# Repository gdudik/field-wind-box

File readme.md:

# Programming the main controller board (USB-PD controller setup)

I am using a cheapo CH134A programmer board with an alligator clamp for SOIC-8. Example: https://a.co/d/9YnwEmc. This unit needed to be modded per the included instructions to work with an EEPROM chip running at 3.3v.

Binary file `USB_C_PD_controller.bin` was built using the TI Application Customization Tool at https://www.ti.com/tool/USBCPD-APPLICATION-CUSTOMIZATION-TOOL.

Choices used:
- Device Type: TPS25751
- Choose TPS 25751S under _Are you a 5V @ 3A power source (provider) only?_
- Highest supported USB Speed: USB 2
- Preferred data role: Device/Upstream Facing Port
- Support BC 1.2? No
- Liquid detection on Type C Connector? No
- Vendor ID and Desired Product ID: TI Vendor ID/0x0000 Product ID

After downloading the bin file from the tool, I used IMS_Prog which is a tool for Mac that will interface with the CH134A. On PC there are other tools, but you'll have to Google. IMS_Prog supposedly also works on Linux.

# Wiring

## 4-Pin Header to XLR
| 4 Pin Header | Wire Color  | Function  | XLR Pin Num  |
|---|---|---|---|
| 1  | Red  | Wind Gauge +12v  | 2  |
|  2 | Black  | Wind Gauge Pwr GND  | Shell  |
| 3  | Green  | Data RX from WG  | 3  |
|  4 |  White | Data GND  | 1  |

## 3-Pin Header to LP16 for RS232
| 3 Pin Header | Wire Color  | Function  | LP16 Pin Num  |
|---|---|---|---|
| 1  | Orange  | RXI  | 2  |
|  2 | White  | Data GND  | 3  |
| 3  | Blue  | TXO  | 1  |

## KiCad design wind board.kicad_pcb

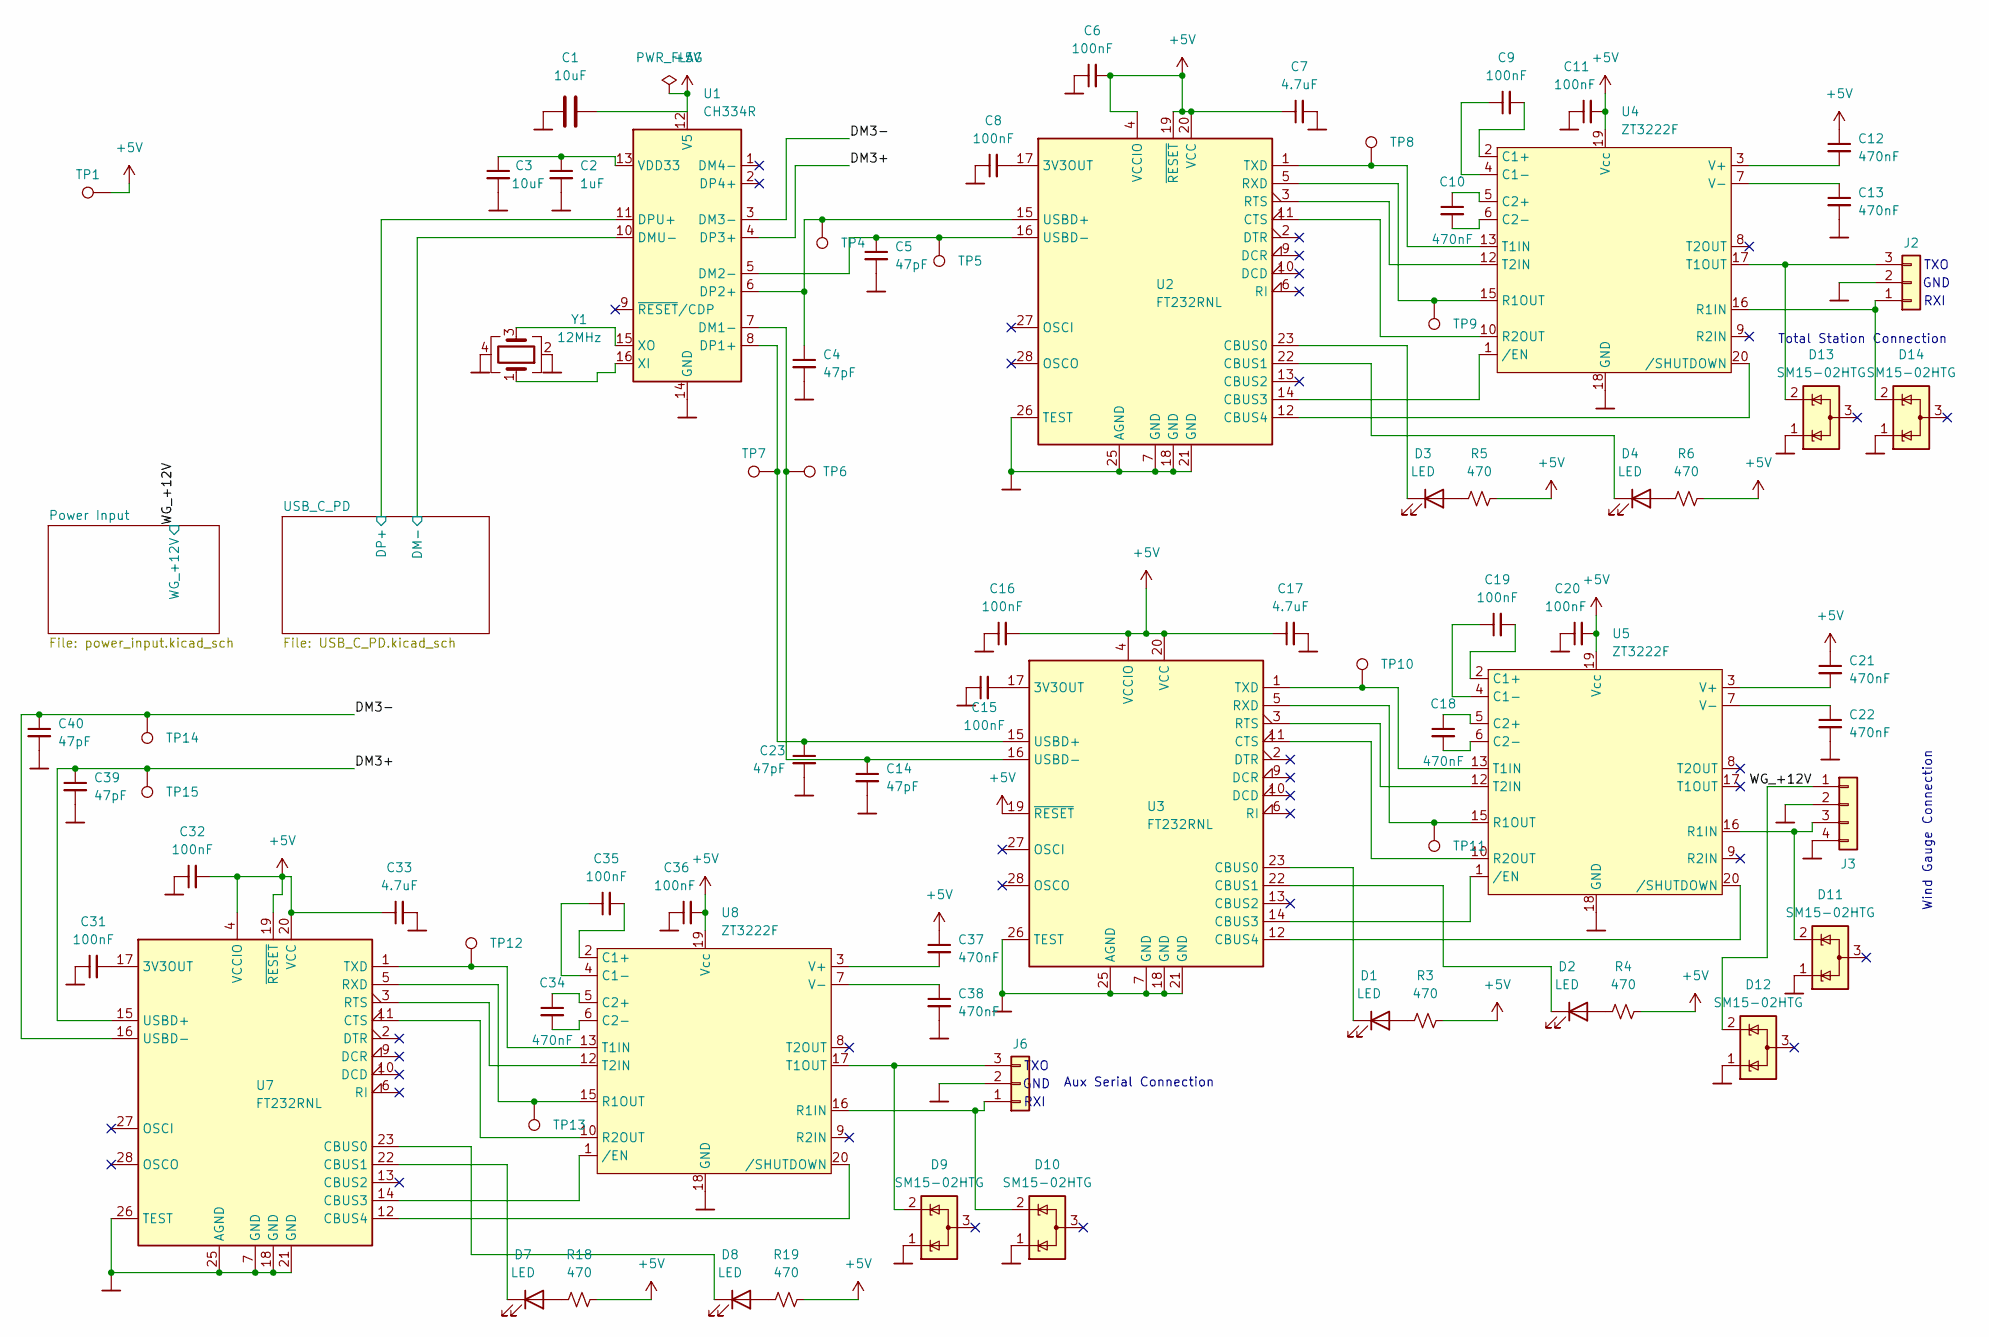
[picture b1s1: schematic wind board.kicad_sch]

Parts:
C1, C3: 10uF; C_0402_1005Metric
C2: 1uF; C_0402_1005Metric
C4, C5: 47pF; C_0603_1608Metric
C6, C8, C9, C11, C15, C16, C19, C20, C31, C32, C35, C36: 100nF; C_0402_1005Metric
C7, C33: 4.7uF; C_0603_1608Metric
C10, C12, C13, C18, C21, C22, C34, C37, C38: 470nF; C_0603_1608Metric
C14, C23, C39, C40: 47pF; C_0402_1005Metric
C17: 4.7uF; C_0402_1005Metric
D1, D2, D3, D4, D7, D8: LED; LED_0603_1608Metric
D9, D10, D11, D12, D13, D14: SM15-02HTG; SM0502HTG
J2, J6: Conn_01x06_MountingPin; PinHeader_1x03_P2.54mm_Horizontal
J3: Conn_01x06_MountingPin; PinHeader_1x04_P2.54mm_Horizontal
R3, R4, R5, R6, R18, R19: 470; R_0402_1005Metric
TP1, TP4, TP5, TP6, TP7, TP8, TP9, TP10, TP11, TP12, TP13, TP14, TP15: TestPoint; TestPoint_THTPad_1.0x1.0mm_Drill0.5mm
U1: CH334R; QSOP-16_3.9x4.9mm_P0.635mm
U2, U3, U7: FT232RNL; SSOP-28_5.3x10.2mm_P0.65mm
U4, U5, U8: ZT3222F; TSSOP-20_4.4x6.5mm_P0.65mm
Y1: 12MHz; Crystal_SMD_3225-4Pin_3.2x2.5mm

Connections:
+5V: C1.2, C6.2, C7.1, C11.2, C12.1, C16.2, C17.1, C20.2, C21.1, C32.2, C33.1, C36.2, C37.1, R3.2, R4.2, R5.2, R6.2, R18.2, R19.2, TP1.1, U1.12 (V5), U2.4 (VCCIO), U2.19 (~RESET), U2.20 (VCC), U3.4 (VCCIO), U3.19 (~RESET), U3.20 (VCC), U4.19 (Vcc), U5.19 (Vcc), U7.4 (VCCIO), U7.19 (~RESET), U7.20 (VCC), U8.19 (Vcc); also elsewhere on the board
/DM3+: C39.1, TP15.1, U1.4 (DP3+), U7.15 (USBD+)
/DM3-: C40.1, TP14.1, U1.3 (DM3-), U7.16 (USBD-)
/USB_C_PD/DM-: U1.10 (DMU-); also elsewhere on the board
/USB_C_PD/DP+: U1.11 (DPU+); also elsewhere on the board
/WG_+12V: D12.2 (K), J3.1; also elsewhere on the board
unnamed: D1.2 (A), R3.1
unnamed: D1.1 (K), U3.23 (CBUS0)
unnamed: D2.2 (A), R4.1
unnamed: D2.1 (K), U3.22 (CBUS1)
unnamed: D3.2 (A), R5.1
unnamed: D3.1 (K), U2.23 (CBUS0)
unnamed: D4.2 (A), R6.1
unnamed: D4.1 (K), U2.22 (CBUS1)
unnamed: D7.2 (A), R18.1
unnamed: D7.1 (K), U7.22 (CBUS1)
unnamed: D8.2 (A), R19.1
unnamed: D8.1 (K), U7.23 (CBUS0)
unnamed: D14.2 (K), J2.1, U4.16 (R1IN)
unnamed: D13.2 (K), J2.3, U4.17 (T1OUT)
unnamed: D11.2 (K), J3.3, U5.16 (R1IN)
unnamed: D10.2 (K), J6.1, U8.16 (R1IN)
unnamed: D9.2 (K), J6.3, U8.17 (T1OUT)
unnamed: C14.1, TP6.1, U1.7 (DM1-), U3.16 (USBD-)
unnamed: C5.1, TP5.1, U1.5 (DM2-), U2.16 (USBD-)
unnamed: C23.1, TP7.1, U1.8 (DP1+), U3.15 (USBD+)
unnamed: C4.1, TP4.1, U1.6 (DP2+), U2.15 (USBD+)
unnamed: C2.1, C3.1, U1.13 (VDD33)
unnamed: U1.16 (XI), Y1.1
unnamed: U1.15 (XO), Y1.3
unnamed: C8.2, U2.17 (3V3OUT)
unnamed: U2.14 (CBUS3), U4.1 (/EN)
unnamed: U2.12 (CBUS4), U4.20 (/SHUTDOWN)
unnamed: U2.11 (CTS), U4.10 (R2OUT)
unnamed: U2.3 (RTS), U4.12 (T2IN)
unnamed: TP9.1, U2.5 (RXD), U4.15 (R1OUT)
unnamed: TP8.1, U2.1 (TXD), U4.13 (T1IN)
unnamed: C15.2, U3.17 (3V3OUT)
unnamed: U3.14 (CBUS3), U5.1 (/EN)
unnamed: U3.12 (CBUS4), U5.20 (/SHUTDOWN)
unnamed: U3.11 (CTS), U5.10 (R2OUT)
unnamed: U3.3 (RTS), U5.12 (T2IN)
unnamed: TP11.1, U3.5 (RXD), U5.15 (R1OUT)
unnamed: TP10.1, U3.1 (TXD), U5.13 (T1IN)
unnamed: C9.2, U4.2 (C1+)
unnamed: C9.1, U4.4 (C1-)
unnamed: C10.1, U4.5 (C2+)
unnamed: C10.2, U4.6 (C2-)
unnamed: C12.2, U4.3 (V+)
unnamed: C13.1, U4.7 (V-)
unnamed: C19.2, U5.2 (C1+)
unnamed: C19.1, U5.4 (C1-)
unnamed: C18.1, U5.5 (C2+)
unnamed: C18.2, U5.6 (C2-)
unnamed: C21.2, U5.3 (V+)
unnamed: C22.1, U5.7 (V-)
unnamed: C31.2, U7.17 (3V3OUT)
unnamed: U7.14 (CBUS3), U8.1 (/EN)
unnamed: U7.12 (CBUS4), U8.20 (/SHUTDOWN)
unnamed: U7.11 (CTS), U8.10 (R2OUT)
unnamed: U7.3 (RTS), U8.12 (T2IN)
unnamed: TP13.1, U7.5 (RXD), U8.15 (R1OUT)
unnamed: TP12.1, U7.1 (TXD), U8.13 (T1IN)
unnamed: C35.2, U8.2 (C1+)
unnamed: C35.1, U8.4 (C1-)
unnamed: C34.1, U8.5 (C2+)
unnamed: C34.2, U8.6 (C2-)
unnamed: C37.2, U8.3 (V+)
unnamed: C38.1, U8.7 (V-)
~: C1.1, C2.2, C3.2, C4.2, C5.2, C6.1, C7.2, C8.1, C11.1, C13.2, C14.2, C15.1, C16.1, C17.2, C20.1, C22.2, C23.2, C31.1, C32.1, C33.2, C36.1, C38.2, C39.2, C40.2, D9.1 (K), D10.1 (K), D11.1 (K), D12.1 (K), D13.1 (K), D14.1 (K), J2.2, J3.2, J3.4, J6.2, U1.14 (GND), U2.7 (GND), U2.18 (GND), U2.21 (GND), U2.25 (AGND), U2.26 (TEST), U3.7 (GND), U3.18 (GND), U3.21 (GND), U3.25 (AGND), U3.26 (TEST), U4.18 (GND), U5.18 (GND), U7.7 (GND), U7.18 (GND), U7.21 (GND), U7.25 (AGND), U7.26 (TEST), U8.18 (GND), Y1.2, Y1.4; also elsewhere on the board

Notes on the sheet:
Total Station Connection
Aux Serial Connection
GND
TXO
Wind Gauge Connection
RXI

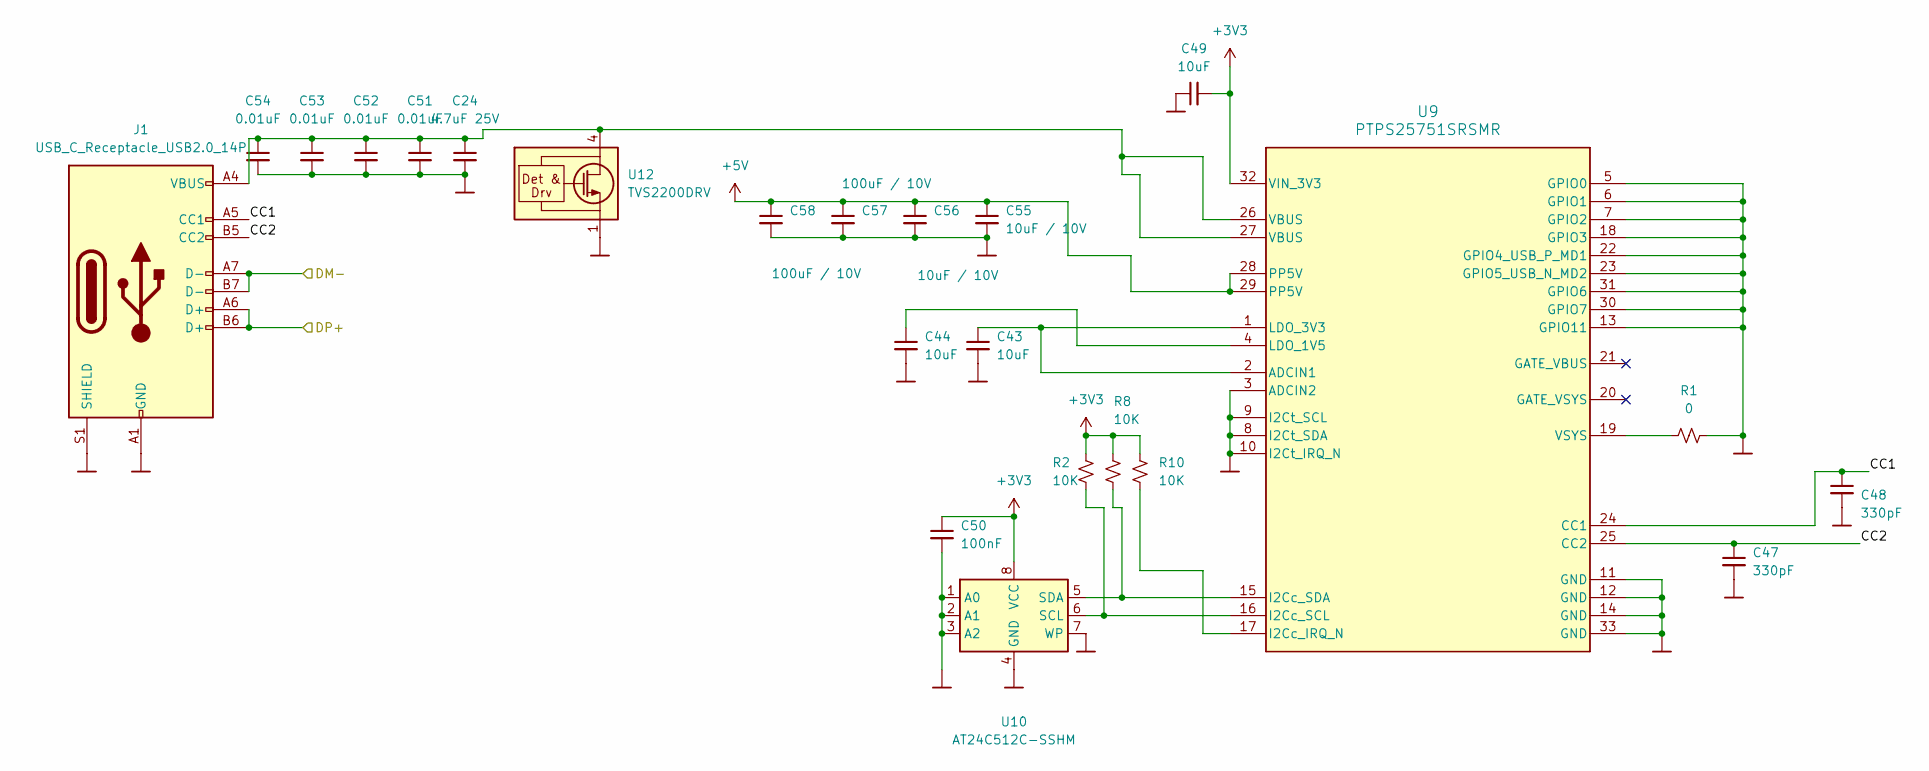
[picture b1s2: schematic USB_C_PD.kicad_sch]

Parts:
C24: 4.7uF 25V; C_0805_2012Metric
C43, C44, C49: 10uF; C_0402_1005Metric
C47, C48: 330pF; C_0603_1608Metric
C50: 100nF; C_0402_1005Metric
C51, C52, C53, C54: 0.01uF; C_0402_1005Metric
C55, C56: 10uF / 10V; C_0603_1608Metric
C57, C58: 100uF / 10V; C_1206_3216Metric
J1: USB_C_Receptacle_USB2.0_14P; USB_C_Receptacle_HRO_TYPE-C-31-M-12
R1: 0; R_0402_1005Metric
R2, R8, R10: 10K; R_0402_1005Metric
U9: PTPS25751SRSMR; RSM0032B-IPC_A
U10: AT24C512C-SSHM; SOIC-8_3.9x4.9mm_P1.27mm
U12: TVS2200DRV; WSON-6-1EP_2x2mm_P0.65mm_EP1x1.6mm

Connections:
+3V3: C49.2, C50.1, R2.1, R8.1, R10.1, U9.32 (VIN_3V3), U10.8 (VCC); also elsewhere on the board
+5V: C55.1, C56.1, C57.1, C58.1, U9.28 (PP5V), U9.29 (PP5V); also elsewhere on the board
/USB_C_PD/CC1: C48.1, J1.A5 (CC1), U9.24 (CC1)
/USB_C_PD/CC2: C47.1, J1.B5 (CC2), U9.25 (CC2)
/USB_C_PD/DM-: J1.A7 (D-), J1.B7 (D-); also elsewhere on the board
/USB_C_PD/DP+: J1.A6 (D+), J1.B6 (D+); also elsewhere on the board
unnamed: C24.1, C51.1, C52.1, C53.1, C54.1, J1.A4 (VBUS), J1.A9 (VBUS), J1.B4 (VBUS), J1.B9 (VBUS), U9.26 (VBUS), U9.27 (VBUS), U12.4 (IN), U12.5 (IN), U12.6 (IN)
unnamed: C43.1, U9.1 (LDO_3V3), U9.2 (ADCIN1)
unnamed: R10.2, U9.17 (I2Cc_IRQ_N)
unnamed: C44.1, U9.4 (LDO_1V5)
unnamed: R1.2, U9.19 (VSYS)
unnamed: R2.2, U9.16 (I2Cc_SCL), U10.6 (SCL)
unnamed: R8.2, U9.15 (I2Cc_SDA), U10.5 (SDA)
~: C24.2, C43.2, C44.2, C47.2, C48.2, C49.1, C50.2, C51.2, C52.2, C53.2, C54.2, C55.2, C56.2, C57.2, C58.2, J1.A1 (GND), J1.A12 (GND), J1.B1 (GND), J1.B12 (GND), J1.S1 (SHIELD), R1.1, U9.3 (ADCIN2), U9.5 (GPIO0), U9.6 (GPIO1), U9.7 (GPIO2), U9.8 (I2Ct_SDA), U9.9 (I2Ct_SCL), U9.10 (I2Ct_IRQ_N), U9.11 (GND), U9.12 (GND), U9.13 (GPIO11), U9.14 (GND), U9.18 (GPIO3), U9.22 (GPIO4_USB_P_MD1), U9.23 (GPIO5_USB_N_MD2), U9.30 (GPIO7), U9.31 (GPIO6), U9.33 (GND), U10.1 (A0), U10.2 (A1), U10.3 (A2), U10.4 (GND), U10.7 (WP), U12.1 (GND), U12.2 (GND), U12.3 (GND), U12.7 (GND); also elsewhere on the board

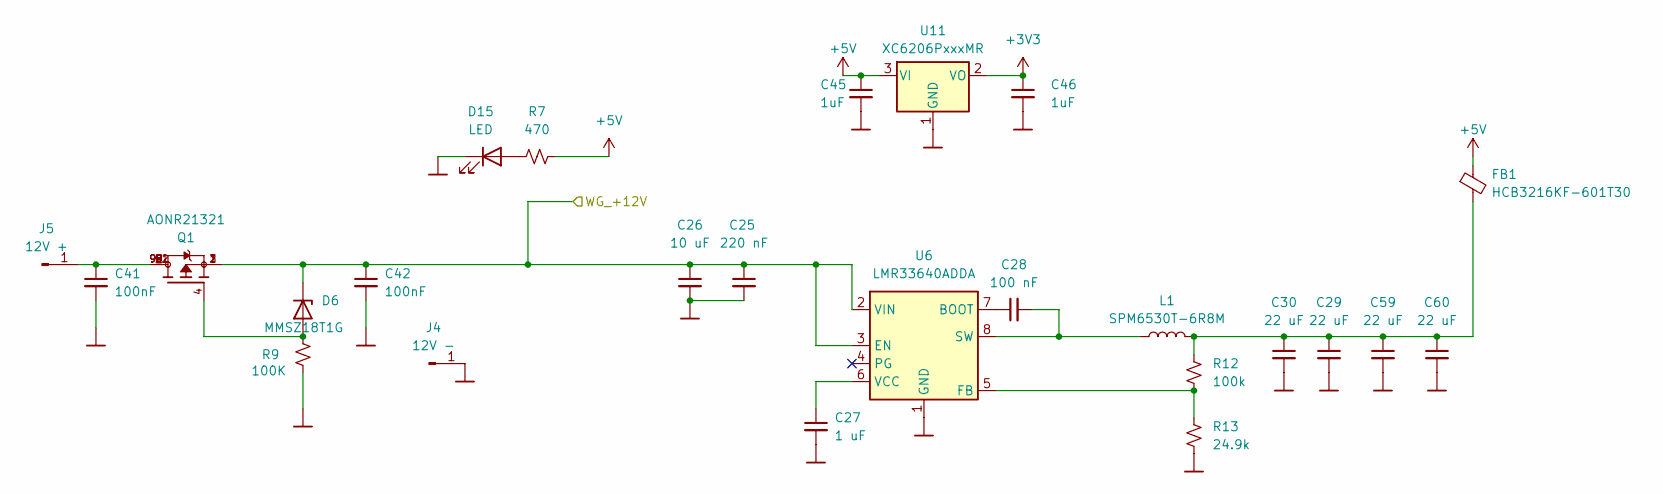
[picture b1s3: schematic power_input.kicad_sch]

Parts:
C25: 220 nF; C_0402_1005Metric
C26: 10 uF; C_0402_1005Metric
C27: 1 uF; C_0402_1005Metric
C28: 100 nF; C_0402_1005Metric
C29, C30, C59, C60: 22 uF; C_0402_1005Metric
C41, C42: 100nF; C_0402_1005Metric
C45, C46: 1uF; C_0402_1005Metric
D6: MMSZ18T1G; D_SOD-123
D15: LED; LED_0603_1608Metric
FB1: HCB3216KF-601T30; C_1206_3216Metric
J4: 12V -; MountingHole_4.3mm_M4_ISO7380_Pad_TopBottom
J5: 12V +; MountingHole_4.3mm_M4_ISO7380_Pad_TopBottom
L1: SPM6530T-6R8M; IND_SPM6530T-2R2M
Q1: AONR21321; TRANS_AONR21321; PARTREV 1.0
R7: 470; R_0402_1005Metric
R9: 100K; R_0402_1005Metric
R12: 100k; C_0402_1005Metric
R13: 24.9k; R_0402_1005Metric
U6: LMR33640ADDA; Texas_HSOP-8-1EP_3.9x4.9mm_P1.27mm_ThermalVias
U11: XC6206PxxxMR; SOT-23-3

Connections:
+3V3: C46.1, U11.2 (VO); also elsewhere on the board
+5V: C45.1, FB1.1, R7.2, U11.3 (VI); also elsewhere on the board
/WG_+12V: C25.1, C26.1, C42.1, D6.1 (K), Q1.1, Q1.2, Q1.3, U6.2 (VIN), U6.3 (EN); also elsewhere on the board
unnamed: C29.1, C30.1, C59.1, C60.1, FB1.2, L1.2, R12.1
unnamed: D6.2 (A), Q1.4, R9.2
unnamed: D15.2 (A), R7.1
unnamed: C41.1, J5.1, Q1.5, Q1.6, Q1.7, Q1.8, Q1.9, Q1.9_1, Q1.9_2
unnamed: C28.1, U6.7 (BOOT)
unnamed: R12.2, R13.1, U6.5 (FB)
unnamed: C28.2, L1.1, U6.8 (SW)
unnamed: C27.1, U6.6 (VCC)
~: C25.2, C26.2, C27.2, C29.2, C30.2, C41.2, C42.2, C45.2, C46.2, C59.2, C60.2, D15.1 (K), J4.1, R9.1, R13.2, U6.1 (GND), U6.9 (GND), U11.1 (GND); also elsewhere on the board

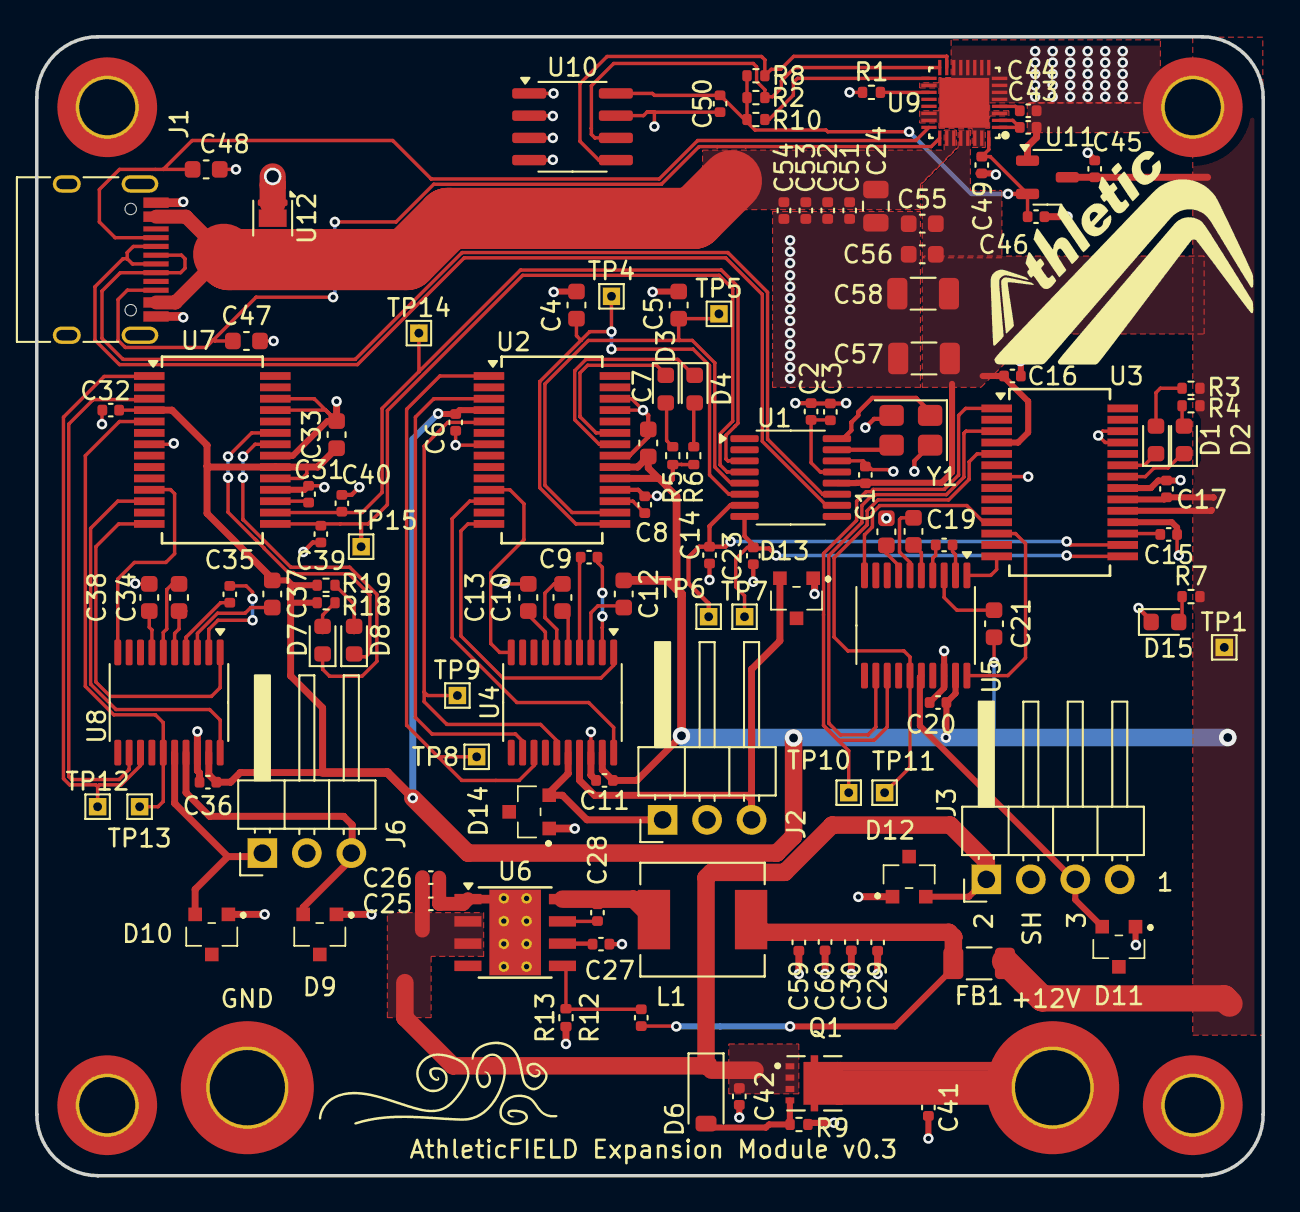
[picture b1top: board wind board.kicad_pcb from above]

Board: 2 copper layers, 70.1 x 65.1 mm, 123 parts (0 on the bottom side), 88 nets.

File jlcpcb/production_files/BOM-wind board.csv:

Comment,Designator,Footprint,LCSC,Quantity
0,R1,R_0402_1005Metric,C17168,1
0.01uF,"C51,C52,C53,C54",C_0402_1005Metric,C15195,4
100K,R9,R_0402_1005Metric,C25741,1
100nF,"C11,C15,C16,C19,C20,C27,C31,C32,C35,C36,C41,C42,C50,C6,C8,C9",C_0402_1005Metric,C1525,16
100uF / 10V,"C57,C58",C_1206_3216Metric,C7432784,2
10K,"R10,R2,R8",R_0402_1005Metric,C25744,3
10uF,"C1,C25,C26,C3,C43,C44,C49",C_0402_1005Metric,C15525,7
10uF / 10V,"C55,C56",C_0603_1608Metric,C19702,2
12MHz,Y1,Crystal_SMD_3225-4Pin_3.2x2.5mm,C9002,1
1N4148WS,D5,D_SOD-323,C2128,1
1uF,"C2,C45,C46",C_0402_1005Metric,C52923,3
20K,R11,R_0402_1005Metric,C25765,1
220K,R13,R_0603_1608Metric,C22961,1
22uF,"C28,C29,C30",C_0603_1608Metric,C59461,3
30K,"R12,R14",R_0603_1608Metric,C22984,2
330pF,"C47,C48",C_0603_1608Metric,C1664,2
4.7uF,"C33,C7",C_0603_1608Metric,C19666,2
4.7uF,C17,C_0402_1005Metric,C23733,1
4.7uF 25V,C24,C_0805_2012Metric,C1779,1
470,"R18,R19,R3,R4,R5,R6,R7",R_0402_1005Metric,C25117,7
470nF,"C10,C12,C13,C18,C21,C22,C34,C37,C38",C_0603_1608Metric,C1623,9
47pF,"C14,C23,C39,C40",C_0402_1005Metric,C1567,4
47pF,"C4,C5",C_0603_1608Metric,C1671,2
AONR21321,Q1,TRANS_AONR21321,C541711,1
AT24C512C-SSHM,U10,SOIC-8_3.9x4.9mm_P1.27mm,C54668,1
CH334R,U1,QSOP-16_3.9x4.9mm_P0.635mm,C4154405,1
HCB3216KF-601T30,FB1,C_1206_3216Metric,C357023,1
LED,"D15,D2,D4,D7",LED_0603_1608Metric,C2286,4
LED,"D1,D3,D8",LED_0603_1608Metric,C2290,3
MMSZ18T1G,D6,D_SOD-123,C40707,1
PTPS25751SRSMR,U9,RSM0032B-IPC_A,C22460852,1
SM15-02HTG,"D10,D11,D12,D13,D14,D9",SM0502HTG,C1975435,6
SPM6530T-2R2M,L1,IND_SPM6530T-2R2M,C76855,1
TPS565242,U6,SOT6_DRL_TEX-L,C5219270,1
TVS2200DRV,U12,WSON-6-1EP_2x2mm_P0.65mm_EP1x1.6mm,C523793,1
USB_C_Receptacle_USB2.0_14P,J1,USB_C_Receptacle_HRO_TYPE-C-31-M-12,C165948,1
XC6206PxxxMR,U11,SOT-23-3,C5446,1
ZT3222F,"U4,U5,U8",TSSOP-20_4.4x6.5mm_P0.65mm,C19078605,3

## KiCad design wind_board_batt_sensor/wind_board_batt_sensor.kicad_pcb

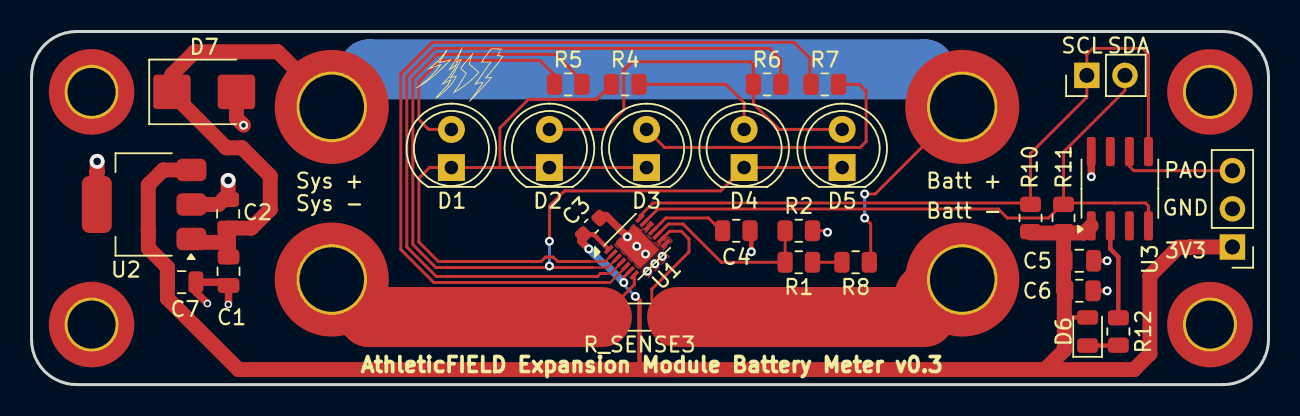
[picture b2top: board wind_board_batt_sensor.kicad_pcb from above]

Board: 2 copper layers, 82.4 x 23.5 mm, 34 parts (0 on the bottom side), 20 nets.

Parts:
C1: 10uF; C_0805_2012Metric
C2, C5: 100nF; C_0805_2012Metric
C3: 100nF; C_0603_1608Metric
C4: 470nF; R_0805_2012Metric
C6: 4.7uF; R_0805_2012Metric
C7: 22uF; C_0805_2012Metric
D1, D2, D3, D4, D5: LED; LED_D5.0mm
D6: LED; LED_0805_2012Metric
D7: SMBJ18A; D_SMB
J1: Batt +; MountingHole_4.3mm_M4_ISO7380_Pad_TopBottom
J2: Batt -; MountingHole_4.3mm_M4_ISO7380_Pad_TopBottom
J3: Sys +; MountingHole_4.3mm_M4_ISO7380_Pad_TopBottom
J4: Sys -; MountingHole_4.3mm_M4_ISO7380_Pad_TopBottom
J5: Conn_01x03_Socket; PinHeader_1x03_P2.54mm_Vertical
J6: Conn_01x02_Socket; PinHeader_1x02_P2.54mm_Vertical
R1: 1.5M - 0.1%; R_0805_2012Metric
R2: 200k - 0.1%; R_0805_2012Metric
R4, R5, R6, R7: 30; R_0805_2012Metric
R8: 300k - 0.1%; R_0805_2012Metric
R10, R11: 10K; R_0805_2012Metric
R12: 150; R_0805_2012Metric
R_SENSE3: 10m; R_1206_3216Metric
U1: MAX17263xxTE; DFN-14-1EP_3x3mm_P0.4mm_EP1.78x2.35mm
U2: TLE42744GS V33; SOT-223
U3: ATtiny402-SS; SOIC-8_3.9x4.9mm_P1.27mm

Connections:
+3.3V: C3.1, C5.2, C6.1, C7.1, D6.2 (A), J5.1, R10.1, R11.1, U1.1 (TH), U1.6 (BATT), U2.3 (Q), U3.1 (VCC)
+12V: C1.1, C2.1, D7.1 (K), J1.1, J3.1, R8.1, U2.1 (I)
unnamed: D1.2 (A), R5.1
unnamed: D1.1 (K), D2.1 (K), D3.1 (K), R4.2, U1.2 (L1)
unnamed: D2.2 (A), D5.2 (A), R6.1
unnamed: D3.2 (A), R7.1
unnamed: D4.2 (A), R4.1
unnamed: D4.1 (K), D5.1 (K), R5.2, U1.3 (L2)
unnamed: D6.1 (K), R12.1
unnamed: J4.1, R_SENSE3.2, U1.7 (CSN)
unnamed: J5.3, U3.6 (~RESET/PA0)
unnamed: J6.1, R10.2, U1.14 (SCL), U3.5 (PA2)
unnamed: J6.2, R11.2, U1.13 (SDA), U3.4 (PA1)
unnamed: R1.1, R8.2
unnamed: R1.2, R2.1, U1.10 (CELLX/CSPH)
unnamed: R6.2, U1.4 (L3)
unnamed: R7.2, U1.5 (L4)
unnamed: C4.1, U1.11 (REG)
unnamed: R12.2, U3.2 (PA6)
~: C1.2, C2.2, C3.2, C4.2, C5.1, C6.2, C7.2, D7.2 (A), J2.1, J5.2, R2.2, R_SENSE3.1, U1.8 (GND), U1.9 (CSPL), U1.12 (ALRT), U1.15 (EP), U2.2 (GND), U2.4 (GND), U3.8 (GND)

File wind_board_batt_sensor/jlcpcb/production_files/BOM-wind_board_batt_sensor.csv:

Comment,Designator,Footprint,LCSC,Quantity
30,R6,R_0805_2012Metric_Pad1.20x1.40mm_HandSolder,,1
10K,R9,R_0805_2012Metric_Pad1.20x1.40mm_HandSolder,,1
100nF,C5,R_0805_2012Metric_Pad1.20x1.40mm_HandSolder,,1
PTSM82903SISB2R,U2,SIS0011A-MFG,,1
TestPoint,J_PA0,TestPoint_Pad_4.0x4.0mm,,1
Batt +,J1,MountingHole_4.3mm_M4_ISO7380_Pad_TopBottom,,1
26.1k,R3,R_0805_2012Metric_Pad1.20x1.40mm_HandSolder,,1
LED,D5,LED_D5.0mm,,1
LED,D2,LED_D5.0mm,,1
LED,D1,LED_D5.0mm,,1
Batt -,J2,MountingHole_4.3mm_M4_ISO7380_Pad_TopBottom,,1
30,R4,R_0805_2012Metric_Pad1.20x1.40mm_HandSolder,,1
MAX17263xxTE,U1,DFN-14-1EP_3x3mm_P0.4mm_EP1.78x2.35mm,,1
22uF,C2,R_0805_2012Metric_Pad1.20x1.40mm_HandSolder,,1
200k - 0.1%,R2,R_0805_2012Metric_Pad1.20x1.40mm_HandSolder,,1
10uF,C1,R_0805_2012Metric_Pad1.20x1.40mm_HandSolder,,1
4.7uF,C6,R_0805_2012Metric_Pad1.20x1.40mm_HandSolder,,1
100 nF,C3,R_0805_2012Metric_Pad1.20x1.40mm_HandSolder,,1
LED,D4,LED_D5.0mm,,1
30,R5,R_0805_2012Metric_Pad1.20x1.40mm_HandSolder,,1
LED,D3,LED_D5.0mm,,1
10K,R11,R_0805_2012Metric_Pad1.20x1.40mm_HandSolder,,1
30,R7,R_0805_2012Metric_Pad1.20x1.40mm_HandSolder,,1
10K,R10,R_0805_2012Metric_Pad1.20x1.40mm_HandSolder,,1
470nF,C4,R_0805_2012Metric_Pad1.20x1.40mm_HandSolder,,1
1.5M - 0.1%,R1,R_0805_2012Metric_Pad1.20x1.40mm_HandSolder,,1
ATtiny402-SS,U3,SOIC-8_3.9x4.9mm_P1.27mm,,1
Sys -,J4,MountingHole_4.3mm_M4_ISO7380_Pad_TopBottom,,1
300k - 0.1%,R8,R_0805_2012Metric_Pad1.20x1.40mm_HandSolder,,1
Sys +,J3,MountingHole_4.3mm_M4_ISO7380_Pad_TopBottom,,1

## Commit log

2025-09-29 test
2025-09-30 added 3rd interface, tvs diodes, charging circuit
2025-09-30 through hole test points
2025-10-14 latest
2025-10-16 starting pd chip
2025-10-16 added footprints, minor deletions
2025-10-17 add usb-c-pd routing
2025-10-17 update capacitors
2025-10-17 aaahhhhhh
2025-10-20 add fuel gauge
2025-10-20 dave's changes
2025-10-21 All components to 0805 on battery board
2025-10-21 add vias
2025-10-22 add silliness
2025-10-27 add pd controller binary for eeprom
2025-11-03 swap sda-scl pins
2025-11-04 add led and sca-scl header
2025-11-04 fix stuff
2025-11-04 moar fixes
2025-11-18 update bom
2025-12-13 new power supply
2025-12-15 add new power supply
2025-12-16 new regulator
2025-12-16 update layout around PSU
2025-12-19 add readme
2025-12-19 more readme
2026-01-22 new buck
2026-01-22 remove pullup resistor
